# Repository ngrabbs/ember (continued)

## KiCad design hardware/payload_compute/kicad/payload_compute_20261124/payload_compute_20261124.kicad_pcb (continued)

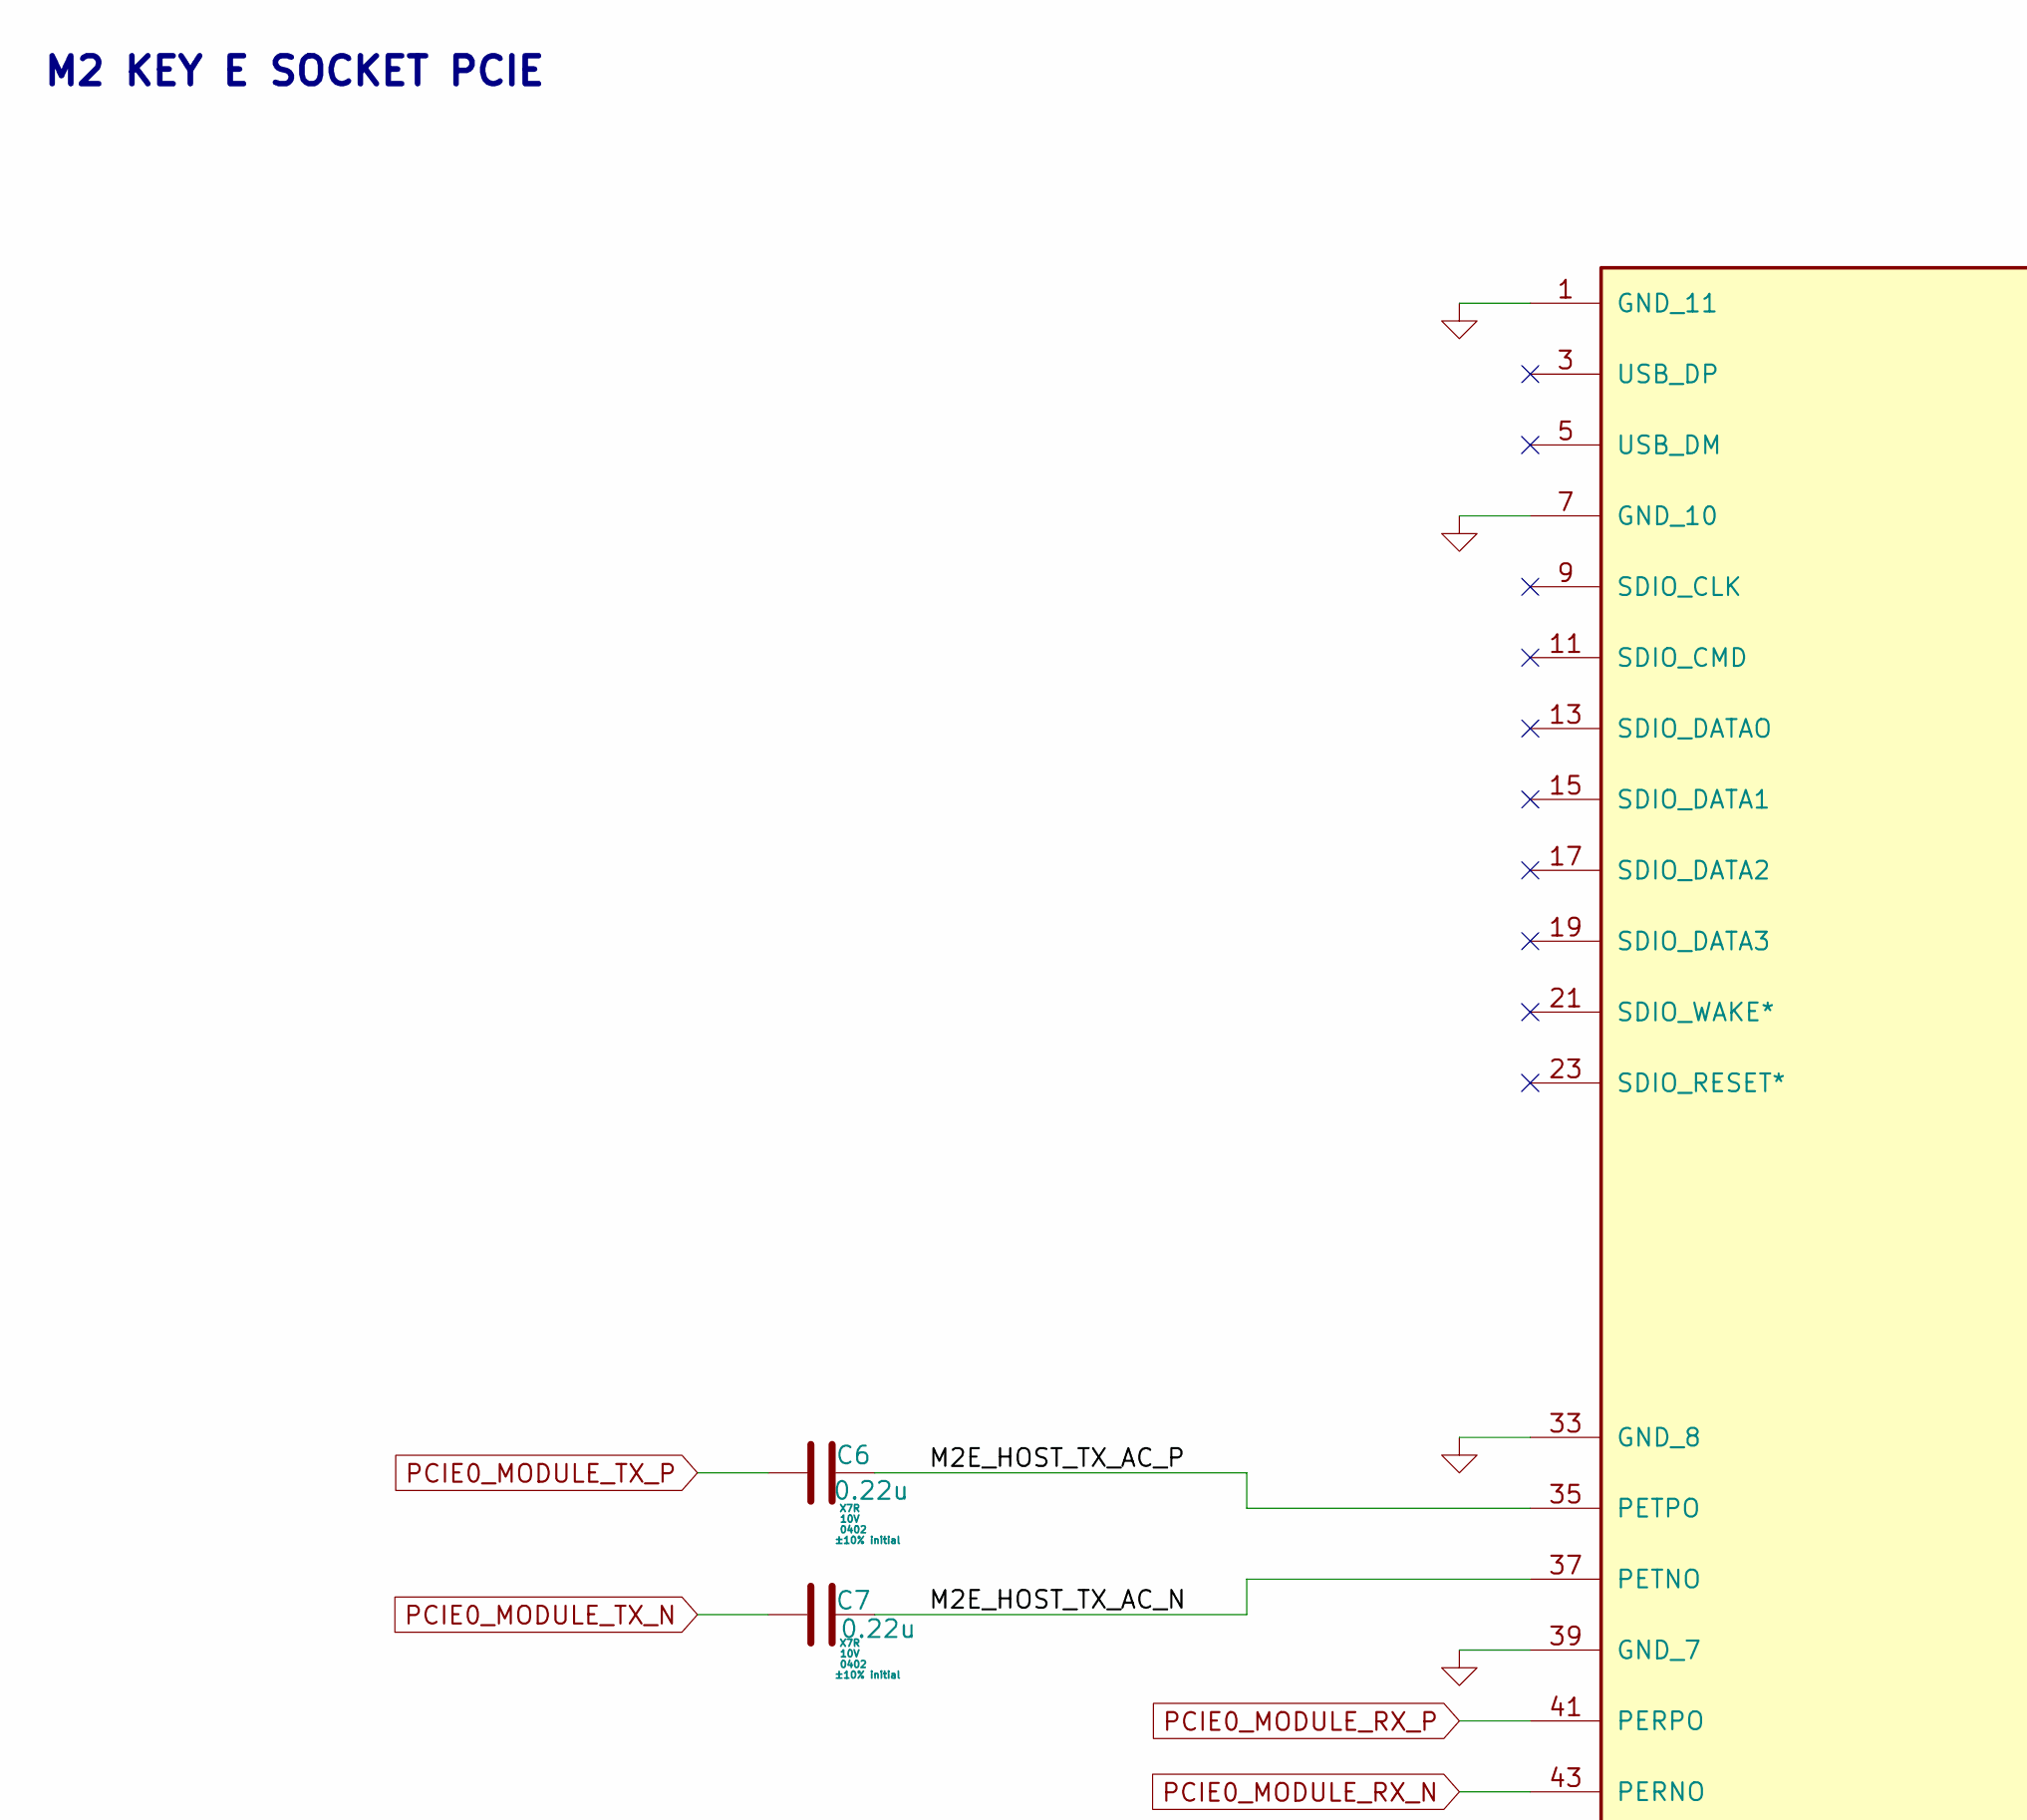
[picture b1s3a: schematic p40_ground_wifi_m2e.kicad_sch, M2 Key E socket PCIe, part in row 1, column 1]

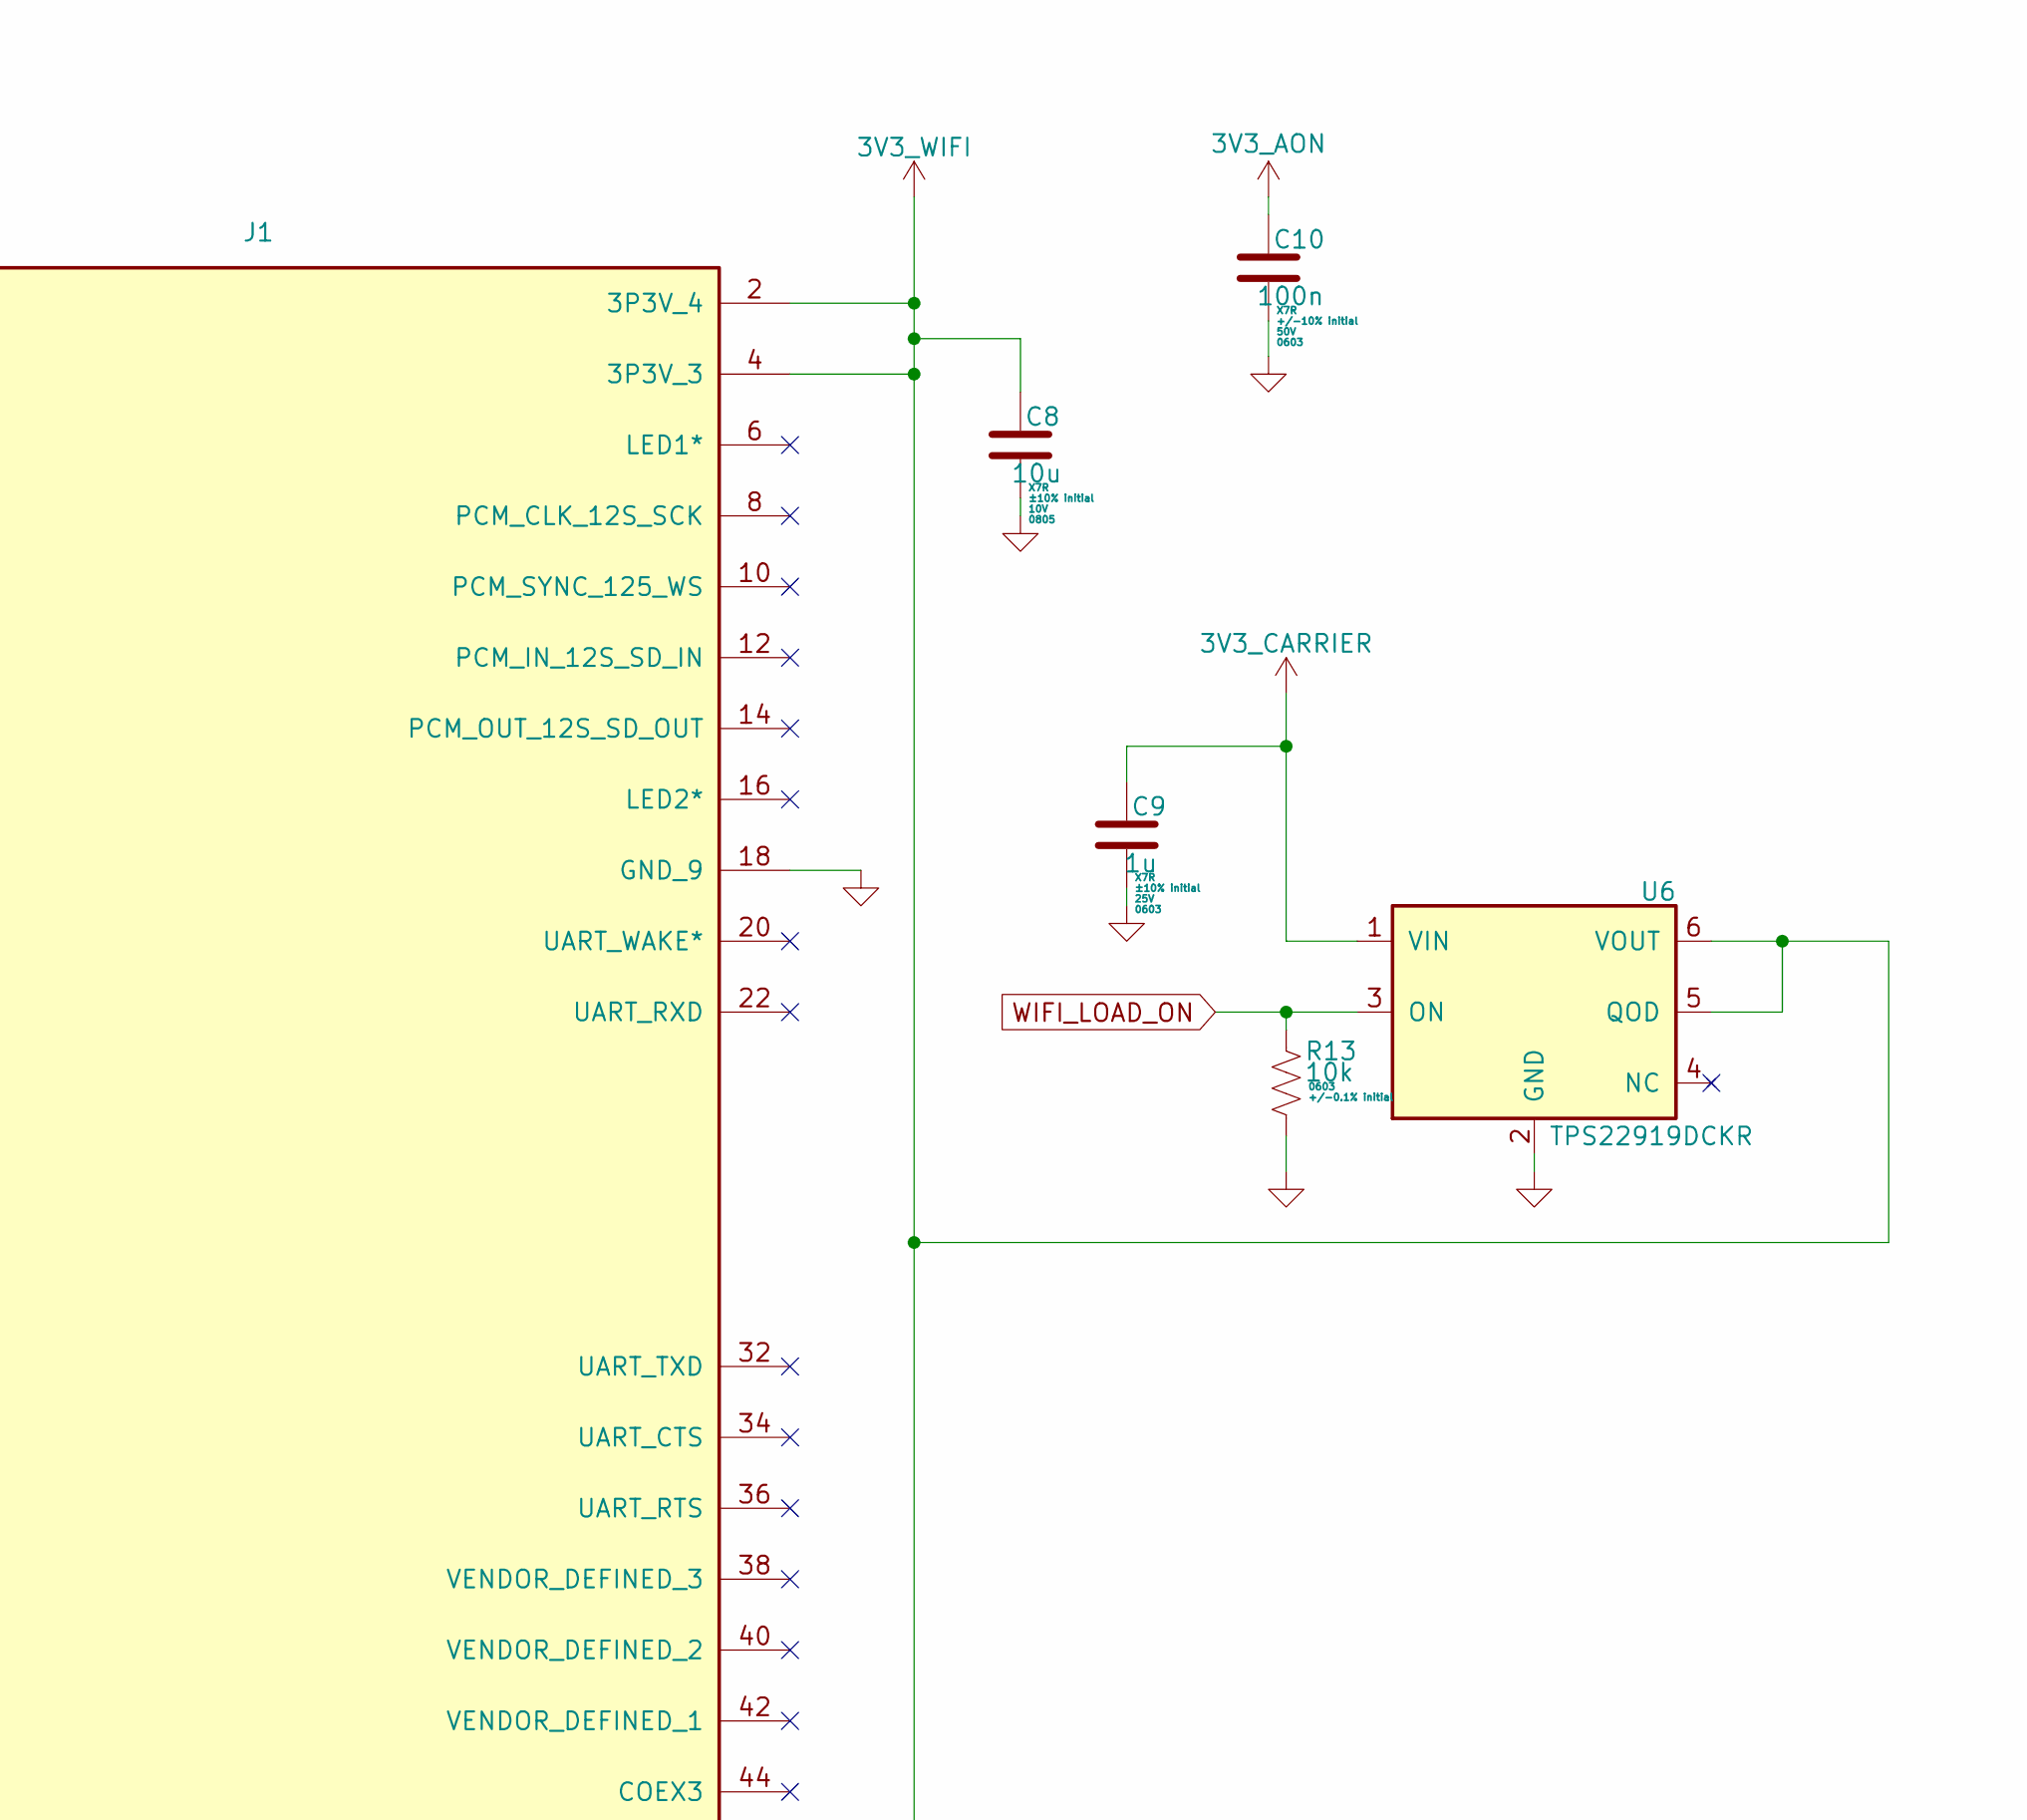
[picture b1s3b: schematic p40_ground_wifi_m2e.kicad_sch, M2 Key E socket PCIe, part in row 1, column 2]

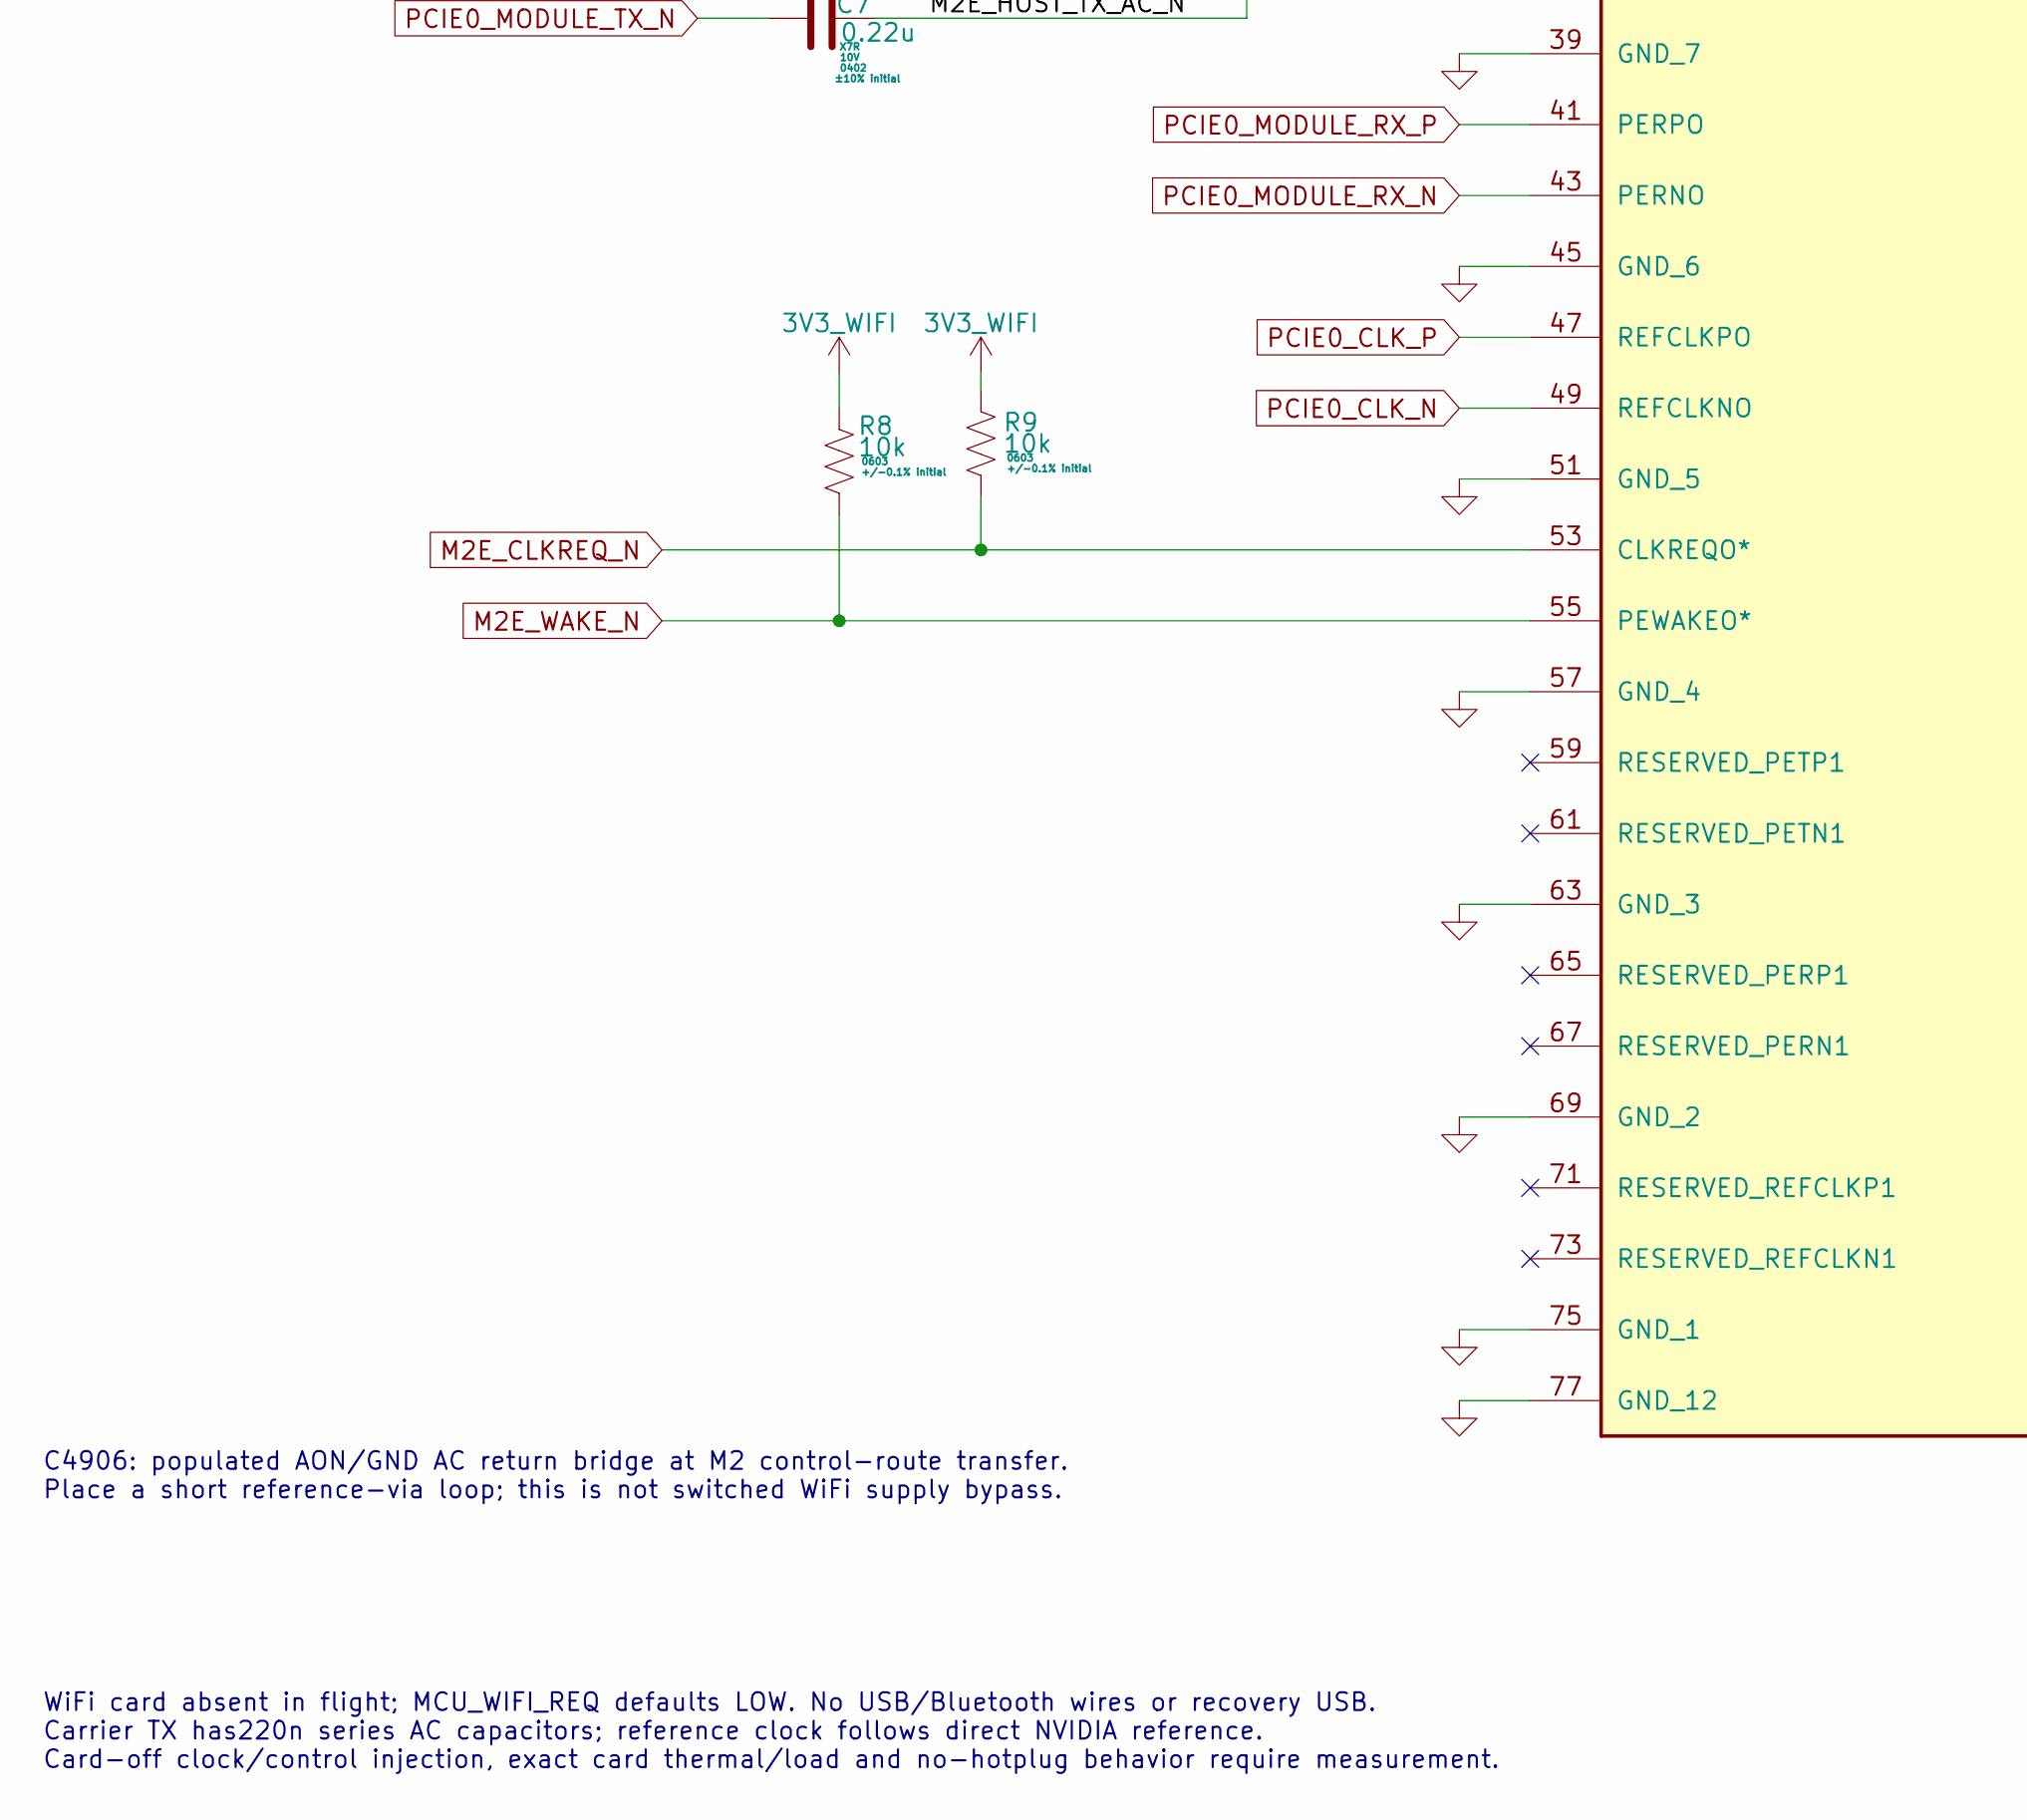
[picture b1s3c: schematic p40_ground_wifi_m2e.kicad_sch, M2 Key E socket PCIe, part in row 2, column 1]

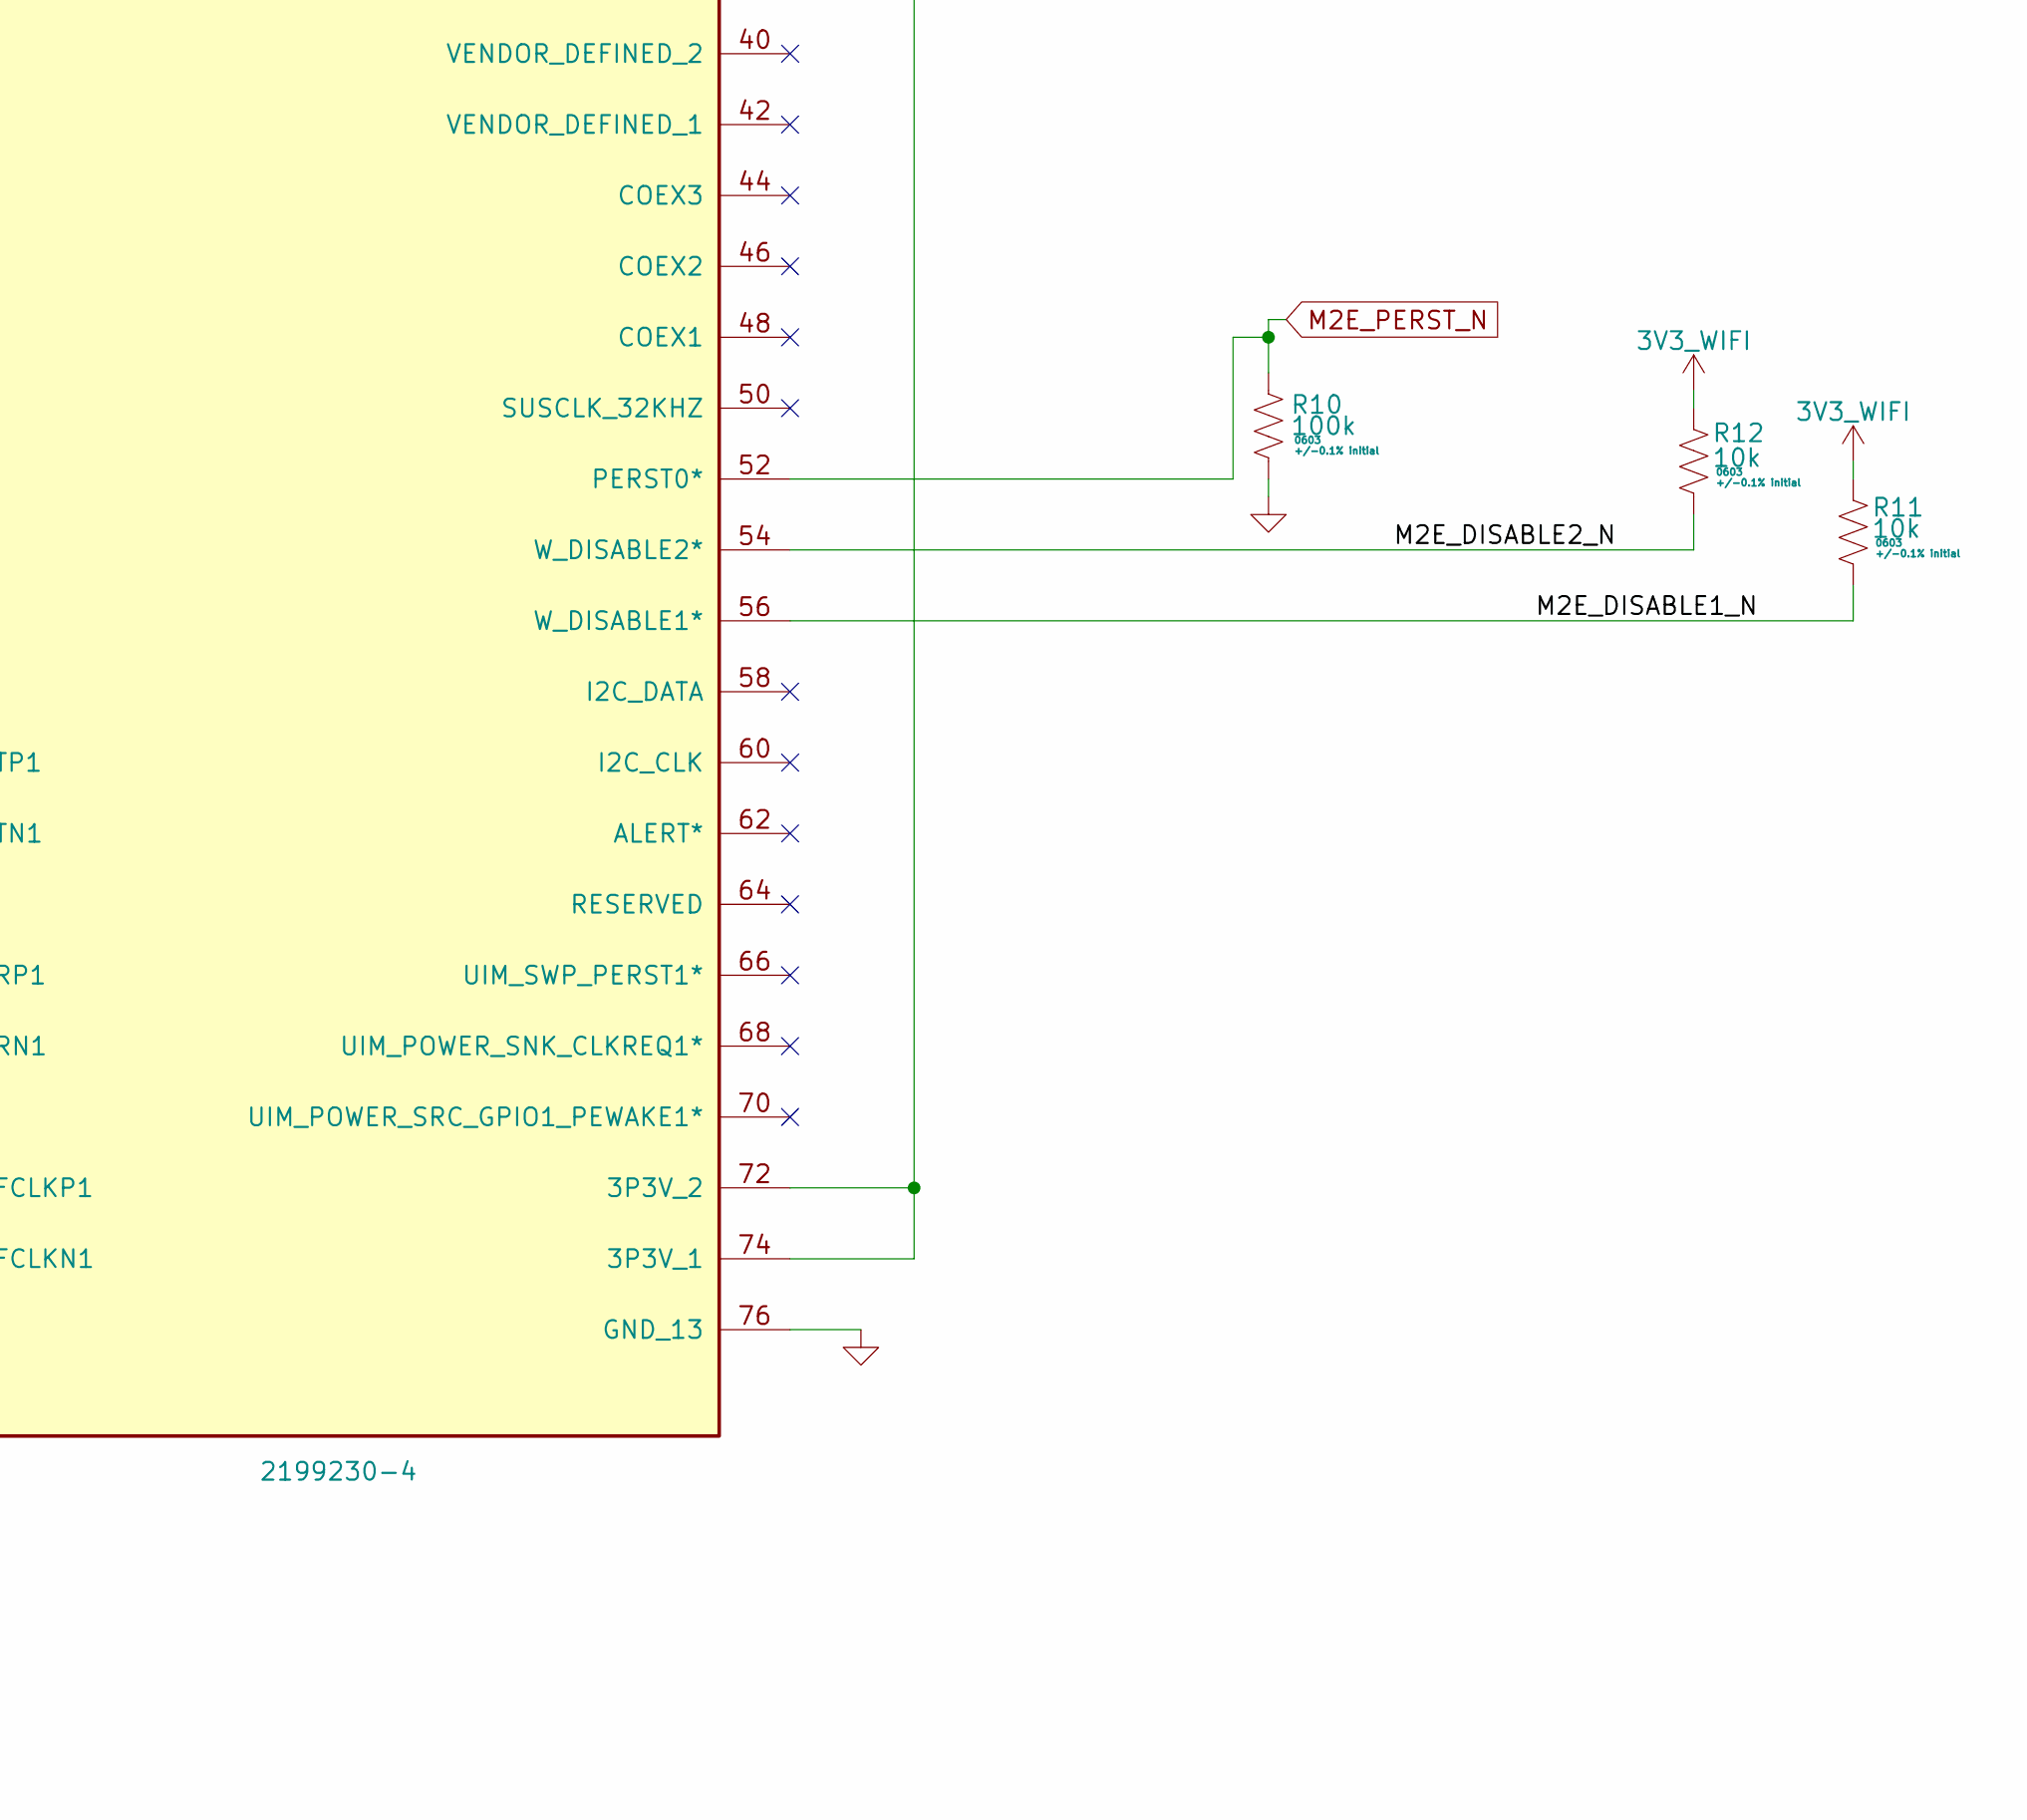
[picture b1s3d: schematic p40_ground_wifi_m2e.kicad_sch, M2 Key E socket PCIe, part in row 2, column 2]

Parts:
C6, C7: 0.22u; C_0402_1005Metric; Tolerance +/-10% initial; Voltage 10V; MFG P/N C0402C224K8RACTU
C8: 10u; C_0805_2012Metric; Tolerance +/-10% initial; Voltage 10V; MFG P/N C0805C106K8RACTU
C9: 1u; C_0603_1608Metric; Tolerance +/-10% initial; Voltage 25V; MFG P/N C0603C105K3RACTU
C10: 100n; C_0603_1608Metric; Tolerance +/-10% initial; Voltage 50V; MFG P/N C0603C104K5RACTU
J1: 2199230-4; TE_2199230_4_KeyE; MPN 2199230-4
R8, R9, R11, R12, R13: 10k; R_0603_1608Metric; Tolerance +/-0.1% initial; MFG P/N TNPW060310K0BEEA
R10: 100k; R_0603_1608Metric; Tolerance +/-0.1% initial; MFG P/N TNPW0603100KBEEA
U6: TPS22919DCKR; TI_DCK0006A; MPN TPS22919DCKR

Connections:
3V3_AON: C10.1; also elsewhere on the board
3V3_CARRIER: C9.1, U6.1 (VIN); also elsewhere on the board
3V3_WIFI: C8.1, J1.2 (3P3V_4), J1.4 (3P3V_3), J1.72 (3P3V_2), J1.74 (3P3V_1), R8.1, R9.1, R11.1, R12.1, U6.5 (QOD), U6.6 (VOUT)
/M2 Key E socket PCIe/M2E_DISABLE1_N: J1.56 (W_DISABLE1*), R11.2
/M2 Key E socket PCIe/M2E_DISABLE2_N: J1.54 (W_DISABLE2*), R12.2
/M2 Key E socket PCIe/M2E_HOST_TX_AC_N: C7.2, J1.37 (PETNO)
/M2 Key E socket PCIe/M2E_HOST_TX_AC_P: C6.2, J1.35 (PETPO)
GND: C8.2, C9.2, C10.2, J1.1 (GND_11), J1.7 (GND_10), J1.18 (GND_9), J1.33 (GND_8), J1.39 (GND_7), J1.45 (GND_6), J1.51 (GND_5), J1.57 (GND_4), J1.63 (GND_3), J1.69 (GND_2), J1.75 (GND_1), J1.76 (GND_13), J1.77 (GND_12), R10.2, R13.2, U6.2 (GND); also elsewhere on the board
M2E_CLKREQ_N: J1.53 (CLKREQO*), R9.2; also elsewhere on the board
M2E_PERST_N: J1.52 (PERST0*), R10.1; also elsewhere on the board
M2E_WAKE_N: J1.55 (PEWAKEO*), R8.2; also elsewhere on the board
PCIE0_CLK_N: J1.49 (REFCLKNO); also elsewhere on the board
PCIE0_CLK_P: J1.47 (REFCLKPO); also elsewhere on the board
PCIE0_MODULE_RX_N: J1.43 (PERNO); also elsewhere on the board
PCIE0_MODULE_RX_P: J1.41 (PERPO); also elsewhere on the board
PCIE0_MODULE_TX_N: C7.1; also elsewhere on the board
PCIE0_MODULE_TX_P: C6.1; also elsewhere on the board
WIFI_LOAD_ON: R13.1, U6.3 (ON); also elsewhere on the board

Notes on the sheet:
M2 KEY E SOCKET PCIE
C4906: populated AON/GND AC return bridge at M2 control-route transfer. Place a short reference-via loop; this is not switched WiFi supply bypass.
WiFi card absent in flight; MCU_WIFI_REQ defaults LOW. No USB/Bluetooth wires or recovery USB. Carrier TX has220n series AC capacitors; reference clock follows direct NVIDIA reference. Card-off clock/control injection, exact card thermal/load and no-hotplug behavior require measurement.

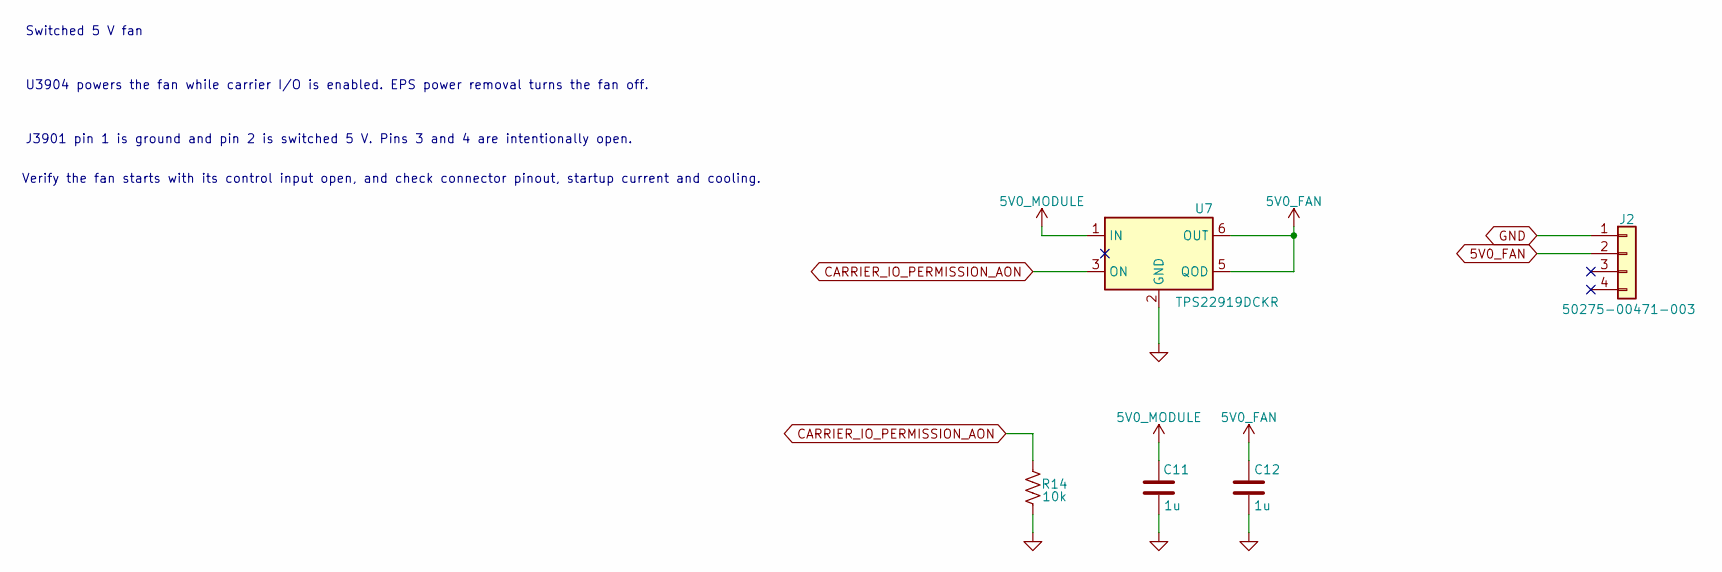
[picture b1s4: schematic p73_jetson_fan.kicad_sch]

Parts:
C11, C12: 1u; C_0603_1608Metric; Tolerance +/-10% initial; Voltage 25V; MFG P/N C0603C105K3RACTU
J2: 50275-00471-003; ACES_50275_00471_003; MFG P/N 50275-00471-003
R14: 10k; R_0603_1608Metric; Tolerance +/-0.1% initial; MFG P/N TNPW060310K0BEEA
U7: TPS22919DCKR; TI_DCK0006A; MFG P/N TPS22919DCKR

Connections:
5V0_FAN: C12.1, J2.2, U7.5 (QOD), U7.6 (OUT)
5V0_MODULE: C11.1, U7.1 (IN); also elsewhere on the board
CARRIER_IO_PERMISSION_AON: R14.1, U7.3 (ON); also elsewhere on the board
GND: C11.2, C12.2, J2.1, R14.2, U7.2 (GND); also elsewhere on the board

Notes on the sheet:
Switched 5 V fan
J3901 pin 1 is ground and pin 2 is switched 5 V. Pins 3 and 4 are intentionally open.
Verify the fan starts with its control input open, and check connector pinout, startup current and cooling.
U3904 powers the fan while carrier I/O is enabled. EPS power removal turns the fan off.

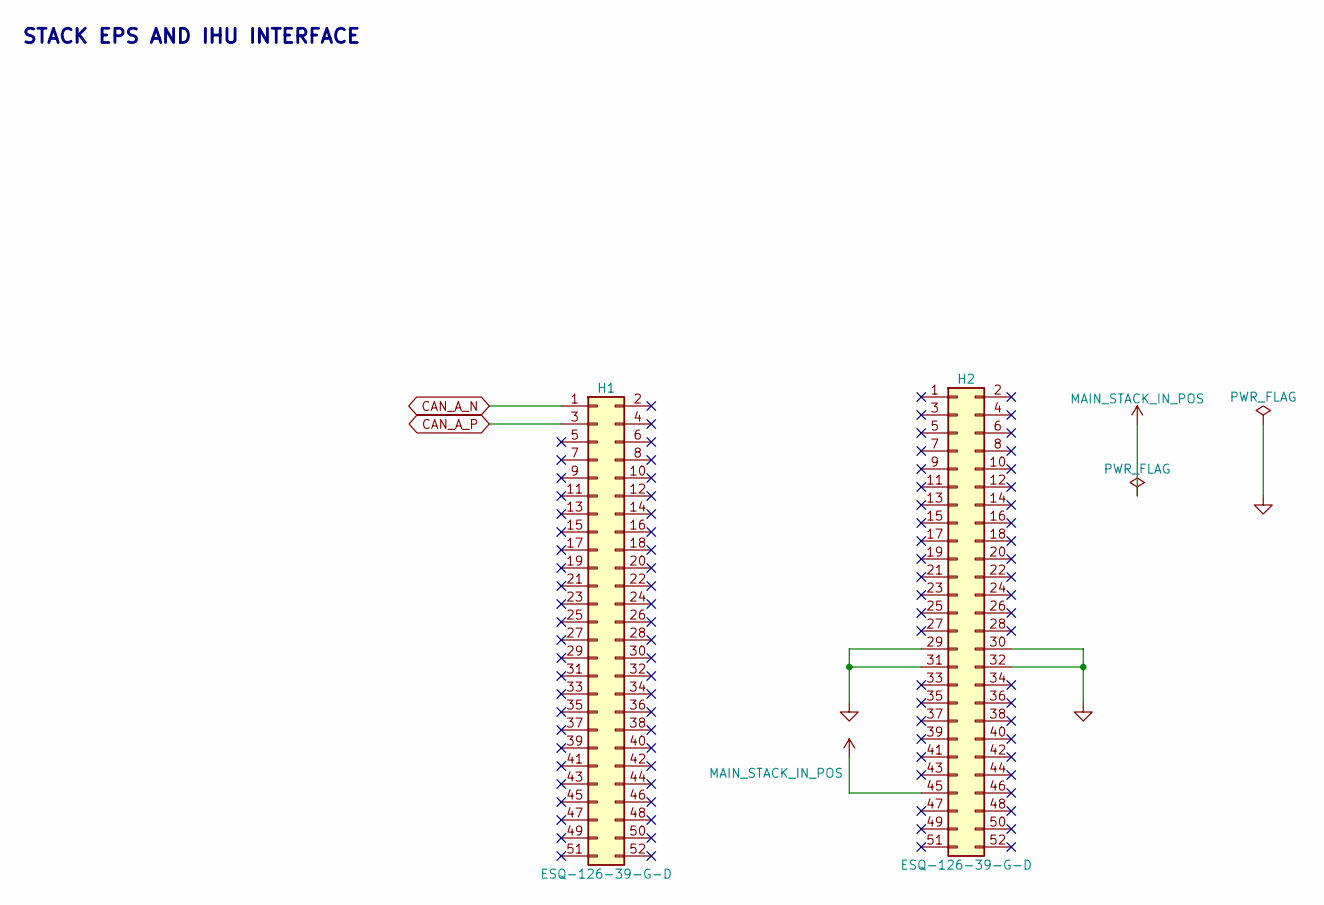
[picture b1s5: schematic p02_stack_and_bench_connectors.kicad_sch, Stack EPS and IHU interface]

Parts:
H1, H2: ESQ-126-39-G-D; Samtec_ESQ_126_39_G_D_CENTERED; MPN ESQ-126-39-G-D

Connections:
CAN_A_N: H1.1; also elsewhere on the board
CAN_A_P: H1.3; also elsewhere on the board
GND: H2.29, H2.30, H2.31, H2.32; also elsewhere on the board
MAIN_STACK_IN_POS: H2.45; also elsewhere on the board

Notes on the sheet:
STACK EPS AND IHU INTERFACE

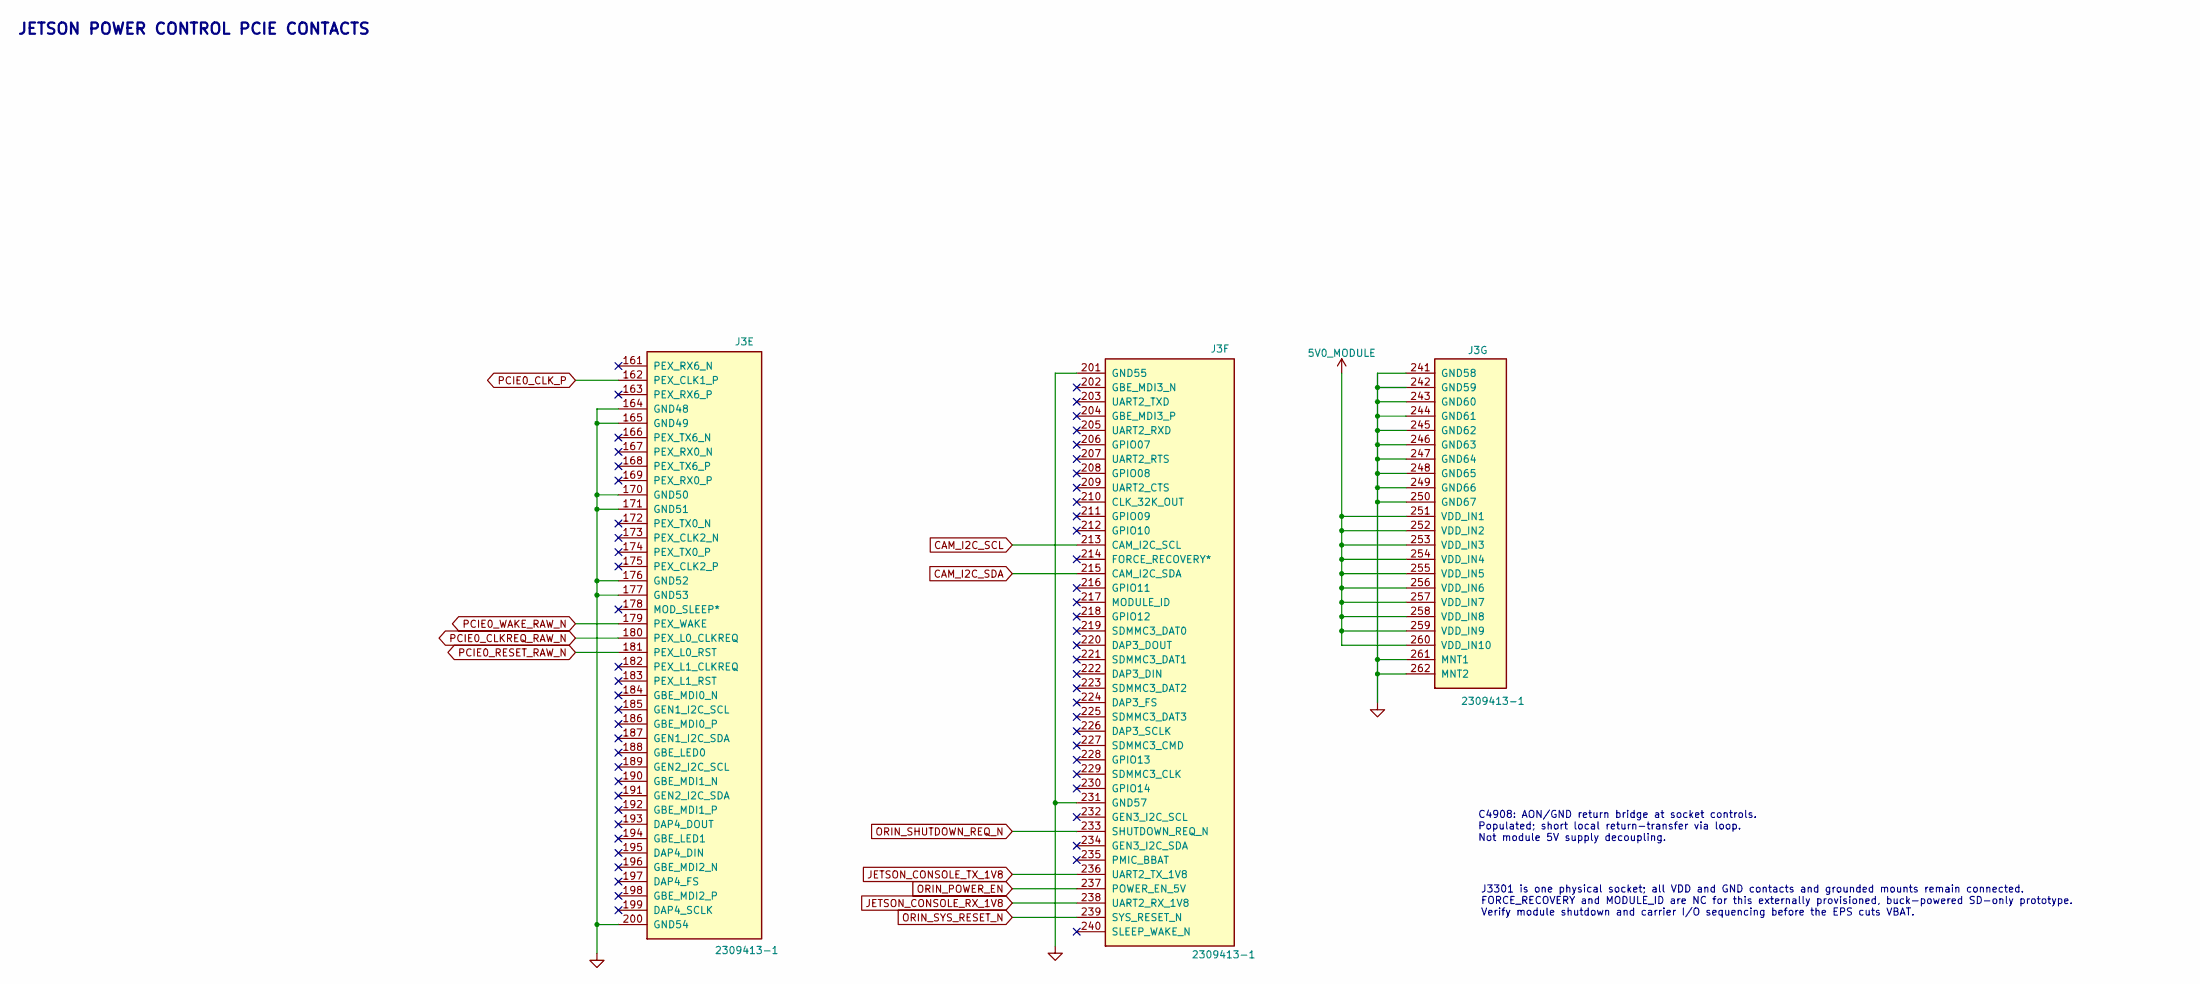
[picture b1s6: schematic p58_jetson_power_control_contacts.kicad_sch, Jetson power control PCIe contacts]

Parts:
J3: 2309413-1; TE_2309413_1; MPN 2309413-1

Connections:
5V0_MODULE: J3.251 (VDD_IN1), J3.252 (VDD_IN2), J3.253 (VDD_IN3), J3.254 (VDD_IN4), J3.255 (VDD_IN5), J3.256 (VDD_IN6), J3.257 (VDD_IN7), J3.258 (VDD_IN8), J3.259 (VDD_IN9), J3.260 (VDD_IN10); also elsewhere on the board
CAM_I2C_SCL: J3.213 (CAM_I2C_SCL); also elsewhere on the board
CAM_I2C_SDA: J3.215 (CAM_I2C_SDA); also elsewhere on the board
GND: J3.164 (GND48), J3.165 (GND49), J3.170 (GND50), J3.171 (GND51), J3.176 (GND52), J3.177 (GND53), J3.200 (GND54), J3.201 (GND55), J3.231 (GND57), J3.241 (GND58), J3.242 (GND59), J3.243 (GND60), J3.244 (GND61), J3.245 (GND62), J3.246 (GND63), J3.247 (GND64), J3.248 (GND65), J3.249 (GND66), J3.250 (GND67), J3.261 (MNT1), J3.262 (MNT2); also elsewhere on the board
JETSON_CONSOLE_RX_1V8: J3.238 (UART2_RX_1V8); also elsewhere on the board
JETSON_CONSOLE_TX_1V8: J3.236 (UART2_TX_1V8); also elsewhere on the board
ORIN_POWER_EN: J3.237 (POWER_EN_5V); also elsewhere on the board
ORIN_SHUTDOWN_REQ_N: J3.233 (SHUTDOWN_REQ_N); also elsewhere on the board
ORIN_SYS_RESET_N: J3.239 (SYS_RESET_N); also elsewhere on the board
PCIE0_CLKREQ_RAW_N: J3.180 (PEX_L0_CLKREQ); also elsewhere on the board
PCIE0_CLK_P: J3.162 (PEX_CLK1_P); also elsewhere on the board
PCIE0_RESET_RAW_N: J3.181 (PEX_L0_RST); also elsewhere on the board
PCIE0_WAKE_RAW_N: J3.179 (PEX_WAKE); also elsewhere on the board

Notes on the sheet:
C4908: AON/GND return bridge at socket controls. Populated; short local return-transfer via loop. Not module 5V supply decoupling.
JETSON POWER CONTROL PCIE CONTACTS
J3301 is one physical socket; all VDD and GND contacts and grounded mounts remain connected. FORCE_RECOVERY and MODULE_ID are NC for this externally provisioned, buck-powered SD-only prototype. Verify module shutdown and carrier I/O sequencing before the EPS cuts VBAT.
